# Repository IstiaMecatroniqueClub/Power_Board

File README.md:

# Istia Mecatronique Club - Power Board

## Synopsis

This repository contains the source codes and the schematics of our power board. 

## Repository architecture

This repository contains a "board" folder with the schematics of the board, a "code" folder with the source code of the ATMega and a "documentation" folder with the doxygen documentation of the source code.

## The source code

### How does it work

The board provide the differents voltages needed in our applications (IstiaBOT). It is also equipped with a CAN interface that allows to request the current and voltage values of the input (batterie) by sending a request CAN message with the ID_POWER_1 (0x091) identifier. The board also raise an alert CAN message (identifier ID_ALERT - 0x080) if the input voltage is too low (batterie with a low level).

### The files

The "code/include" folder contains 
 - a Pin interface class to handle a pin on the ATMega (this class sould not be instanciated)
 - an Input class to handle an input pin
 - an Ouput class to handle an output pin
 - a Led class to handle an led connected to the ATMega

### The ATMega output.hex file
In the code folder you can find a Makefile to generate the binary *.hex file and upload it to the ATMega. The makefile is configured for
 - avrdude compiler ( $ sudo apt-get install avrdude avr-libc)
 - AVRispmkII programmer

Then do
 - $ make hex # to generate the binary ouput.hex
 - $ make upload # to upload the output.hex file to the ATMega
 - $ make all  # to compile and then upload 

This has been tester with Ubuntu and Lubuntu on a raspberry pi 3.

## The documentation
We use Doxygen to generate the documentation of the source code. By using the makefile (in the code folder) you can do
 - $ make documentation
To generate the documentation files.

Note that you need to have doxygen and graphviz (for the graphs) installed
 - $ sudo apt-get install doxygen
 - $ sudo apt-get install graphviz

## Tests

When powering the board, the LEDs should blink a few times and then stop.

## License

GNU General Public License v3.0.

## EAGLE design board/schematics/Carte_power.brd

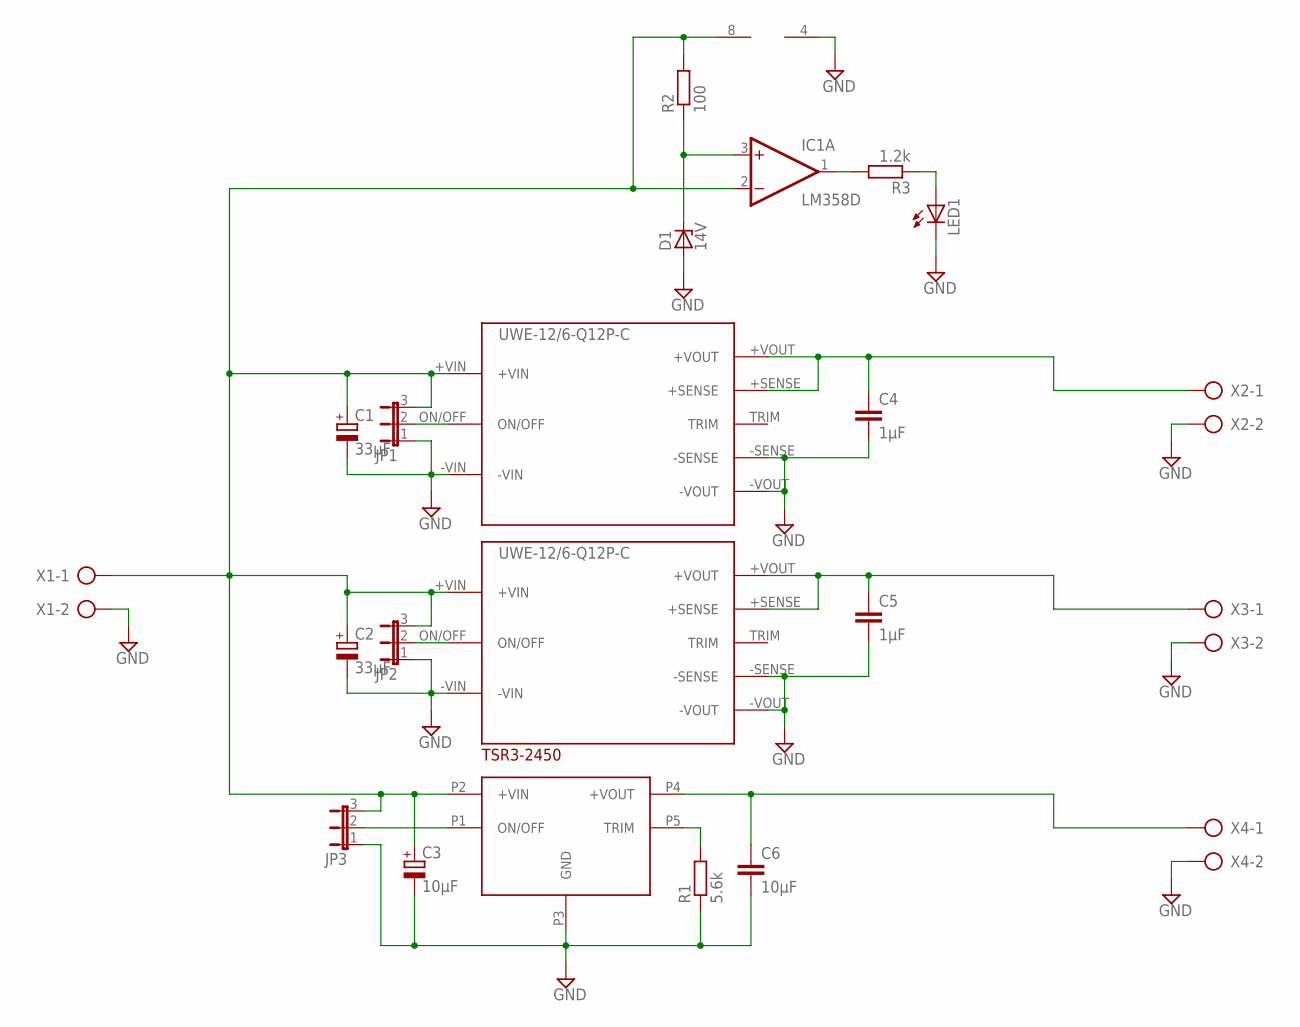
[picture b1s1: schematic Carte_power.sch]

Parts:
C1, C2: 33µF; 153CLV-1010
C3: 10µF; 153CLV-1010
C4, C5: 1µF; C2012
C6: 10µF; C2012
D1: 14V; C1702-15
IC1: LM358D; SO08
JP1, JP2, JP3: JP2E; JP2
LED1: LED5MM
R1: 5.6k; R2012
R2: 100; R2012
R3: 1.2k; R2012
U$1, U$4: UWE-12/6-Q12P-C
U$2: TSR3-2450
X1, X2, X3, X4: AK300/2

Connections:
+VIN: C1.+, C2.+, C3.+, IC1.2 (-IN), IC1.8 (V+), JP1.3, JP2.3, JP3.3, R2.2, U$1.+VIN, U$2.P2 (+VIN), U$4.+VIN, X1.1
GND: C1.-, C2.-, C3.-, C4.2, C5.2, C6.2, D1.A, IC1.4 (V-), JP1.1, JP2.1, JP3.1, LED1.K (C), R1.1, U$1.-SENSE, U$1.-VIN, U$1.-VOUT, U$2.P3 (GND), U$4.-SENSE, U$4.-VIN, U$4.-VOUT, X1.2, X2.2, X3.2, X4.2
unnamed: D1.C, IC1.3 (+IN), R2.1
unnamed: JP1.2, U$4.ON/OFF
unnamed: JP2.2, U$1.ON/OFF
unnamed: R1.2, U$2.P5 (TRIM)
unnamed: C6.1, U$2.P4 (+VOUT), X4.1
unnamed: C5.1, U$1.+SENSE, U$1.+VOUT, X3.1
unnamed: C4.1, U$4.+SENSE, U$4.+VOUT, X2.1
unnamed: JP3.2, U$2.P1 (ON/OFF)
unnamed: IC1.1 (OUT), R3.2
unnamed: LED1.A, R3.1

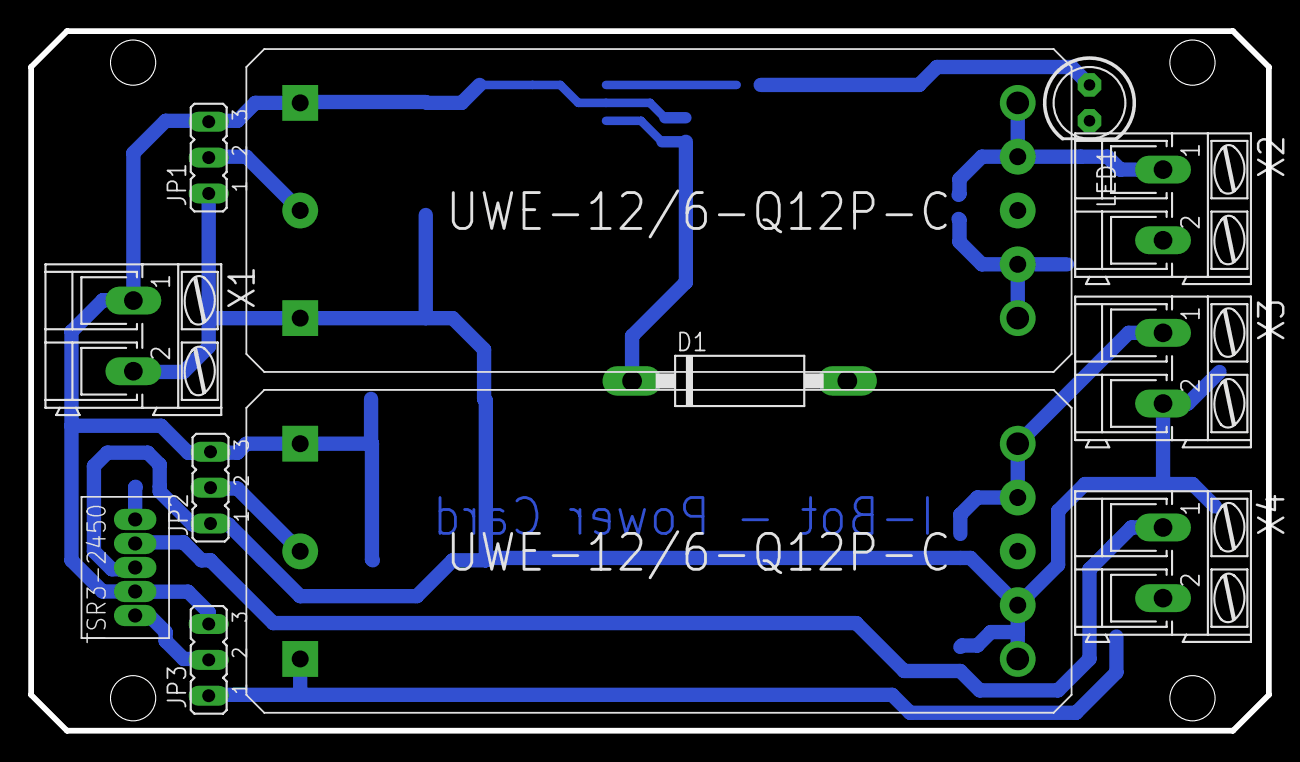
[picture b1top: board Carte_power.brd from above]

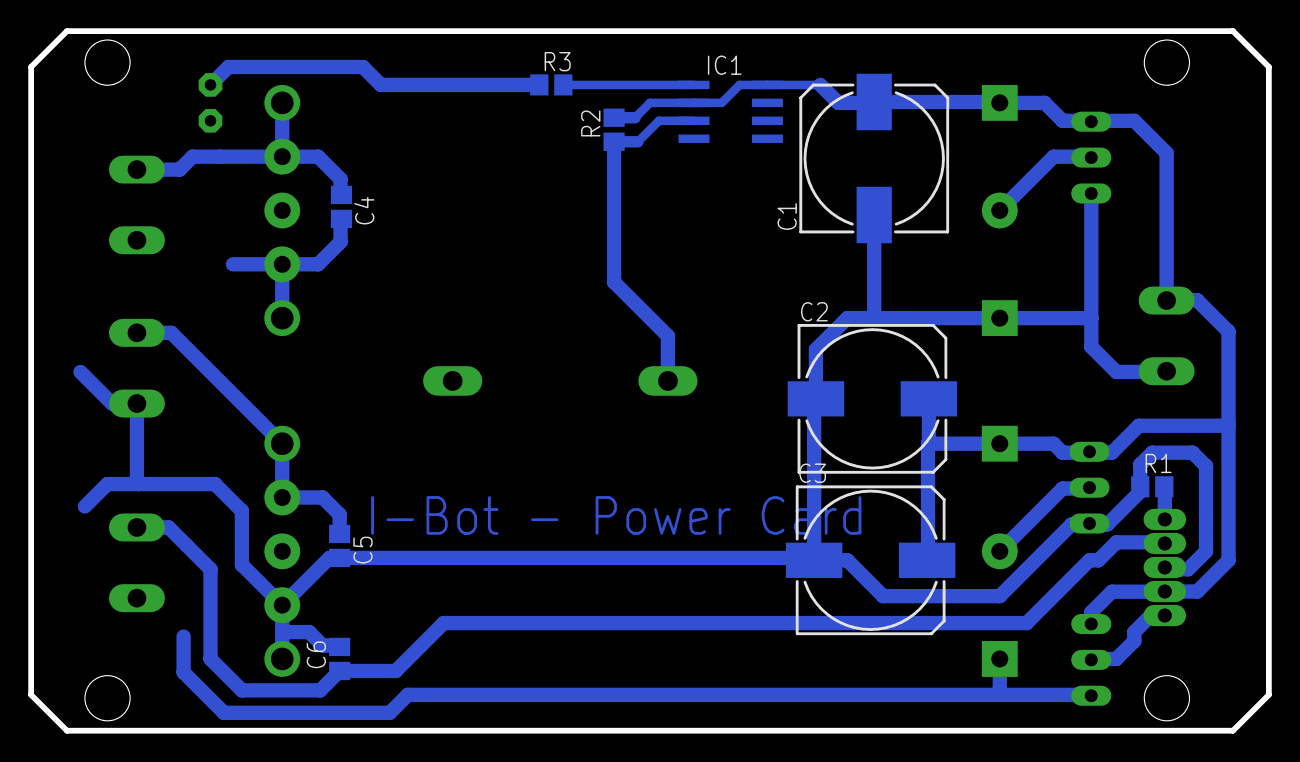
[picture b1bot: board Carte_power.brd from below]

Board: 2 copper layers, 87.6 x 49.5 mm, 22 parts (10 on the bottom side), 12 nets.

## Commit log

2017-06-15 Adding source code and schematics
2017-06-16 readme update
